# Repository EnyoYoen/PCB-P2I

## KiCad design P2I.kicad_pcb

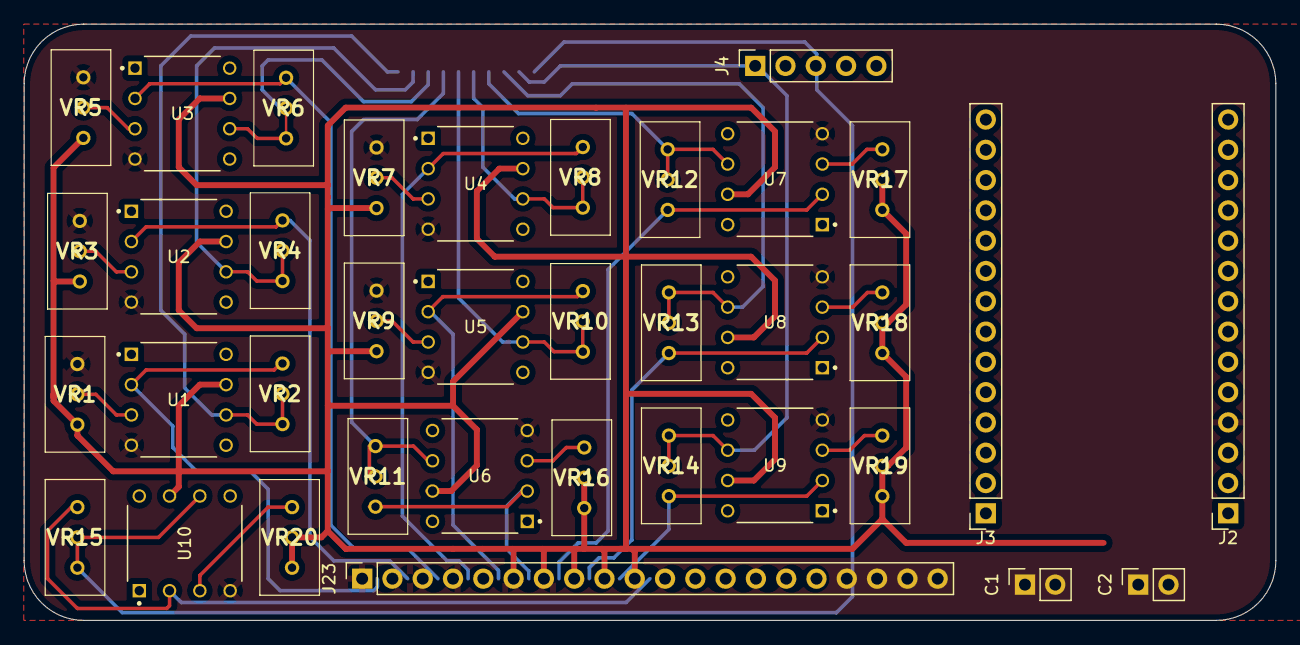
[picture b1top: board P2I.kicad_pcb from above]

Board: 2 copper layers, 105.0 x 50.0 mm, 36 parts (0 on the bottom side), 32 nets.

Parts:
C1: 10uF; PinSocket_1x02_P2.54mm_Vertical
C2: 100nF; PinSocket_1x02_P2.54mm_Vertical
J2, J3: Conn_01x14_Socket; PinSocket_1x14_P2.54mm_Vertical
J4: Conn_01x05_Socket; PinSocket_1x05_P2.54mm_Vertical
J23: Conn_01x20_Socket; PinSocket_1x20_P2.54mm_Vertical
U1, U2, U3, U4, U5, U6, U7, U8, U9, U10: LM741CN_NOPB; DIP794W45P254L959H508Q8
VR1, VR2, VR3, VR4, VR5, VR6, VR7, VR8, VR9, VR10, VR11, VR12, VR13, VR14, VR15, VR16, VR17, VR18, VR19, VR20: T93YA104KT20; T93YA5K10

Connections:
+5V: C1.2, C2.2, J2.1, J23.11, J23.13, J23.15, J23.17, J23.19, U1.7 (V+), U2.7 (V+), U3.7 (V+), U4.7 (V+), U5.7 (V+), U6.7 (V+), U7.7 (V+), U8.7 (V+), U9.7 (V+), U10.7 (V+), VR1.1 (A), VR3.1 (A), VR5.1 (A), VR7.1 (A), VR9.1 (A), VR16.1 (A), VR16.2 (B), VR17.1 (A), VR17.2 (B), VR18.1 (A), VR18.2 (B), VR19.1 (A), VR19.2 (B), VR20.1 (A), VR20.2 (B)
/A1: J3.4, U1.6 (OUTPUT), VR2.1 (A), VR2.2 (B)
/A2: J3.5, U2.6 (OUTPUT), VR4.1 (A), VR4.2 (B)
/A3: J3.6, U3.6 (OUTPUT), VR6.1 (A), VR6.2 (B)
/A4: J3.7, U4.6 (OUTPUT), VR8.1 (A), VR8.2 (B)
/A5: J3.8, U5.6 (OUTPUT), VR10.1 (A), VR10.2 (B)
/A6: J4.1, U6.6 (OUTPUT), VR11.1 (A), VR11.2 (B)
/A7: J4.2, U7.6 (OUTPUT), VR12.1 (A), VR12.2 (B)
/A8: J4.3, U8.6 (OUTPUT), VR13.1 (A), VR13.2 (B)
/A9: J4.4, U9.6 (OUTPUT), VR14.1 (A), VR14.2 (B)
/A10: J4.5, U10.6 (OUTPUT), VR15.1 (A), VR15.2 (B)
/Flex1: J23.12, U6.2 (INV_INPUT), VR11.3 (C)
/Flex2: J23.14, U7.2 (INV_INPUT), VR12.3 (C)
/Flex3: J23.16, U8.2 (INV_INPUT), VR13.3 (C)
/Flex4: J23.18, U9.2 (INV_INPUT), VR14.3 (C)
/Flex5: J23.20, U10.2 (INV_INPUT), VR15.3 (C)
/Force1: J23.2, U1.2 (INV_INPUT), VR2.3 (C)
/Force2: J23.4, U2.2 (INV_INPUT), VR4.3 (C)
/Force3: J23.6, U3.2 (INV_INPUT), VR6.3 (C)
/Force4: J23.8, U4.2 (INV_INPUT), VR8.3 (C)
/Force5: J23.10, U5.2 (INV_INPUT), VR10.3 (C)
GND: C1.1, C2.1, J2.4, J23.1, J23.3, J23.5, J23.7, J23.9, U1.4 (V-), U2.4 (V-), U3.4 (V-), U4.4 (V-), U5.4 (V-), U6.4 (V-), U7.4 (V-), U8.4 (V-), U9.4 (V-), U10.4 (V-), VR1.3 (C), VR3.3 (C), VR5.3 (C), VR7.3 (C), VR9.3 (C)
unnamed: U1.3 (NON-INV_INPUT), VR1.2 (B)
unnamed: U2.3 (NON-INV_INPUT), VR3.2 (B)
unnamed: U3.3 (NON-INV_INPUT), VR5.2 (B)
unnamed: U4.3 (NON-INV_INPUT), VR7.2 (B)
unnamed: U5.3 (NON-INV_INPUT), VR9.2 (B)
unnamed: U6.3 (NON-INV_INPUT), VR16.3 (C)
unnamed: U7.3 (NON-INV_INPUT), VR17.3 (C)
unnamed: U8.3 (NON-INV_INPUT), VR18.3 (C)
unnamed: U9.3 (NON-INV_INPUT), VR19.3 (C)
unnamed: U10.3 (NON-INV_INPUT), VR20.3 (C)

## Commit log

2024-03-23 Init repo
